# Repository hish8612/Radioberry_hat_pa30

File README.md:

# [Radioberry_hat_pa30](https://github.com/hish8612/Radioberry_hat_pa30)

beta0.2 Release

This project provides a preamplifier to drive a [30W-PA (HL2-PA30 by ji1udd)](https://github.com/ji1udd/HL2-PA30) for Radioberry-2. It will be plugged on top of the radioberry-2.<br>

#### Feature
・Preamplifire(OPA2674) based on [radioberry.hat](https://github.com/pa3gsb/Radioberry-2.x/tree/master/hardware/hat)<br>
・On board ADC(MAX11613) for measuring pa-current, temperature and pa-fwd/rev from HL2-PA30 board. <br>
・Paddle or straight key inputs and PTT(Key) inputs.<br>
・No-latency sidetone output at [local CW operation.](https://github.com/hish8612/Hermes-Lite2/tree/master/gateware/variants/radioberry_cl025_cwsidetone)<br>

#### Board View

<br>

#### Connection diagram (beta0.1)

<br>

#### HL2-PA30 modifications.

#### PA30 mesurements.

// end item

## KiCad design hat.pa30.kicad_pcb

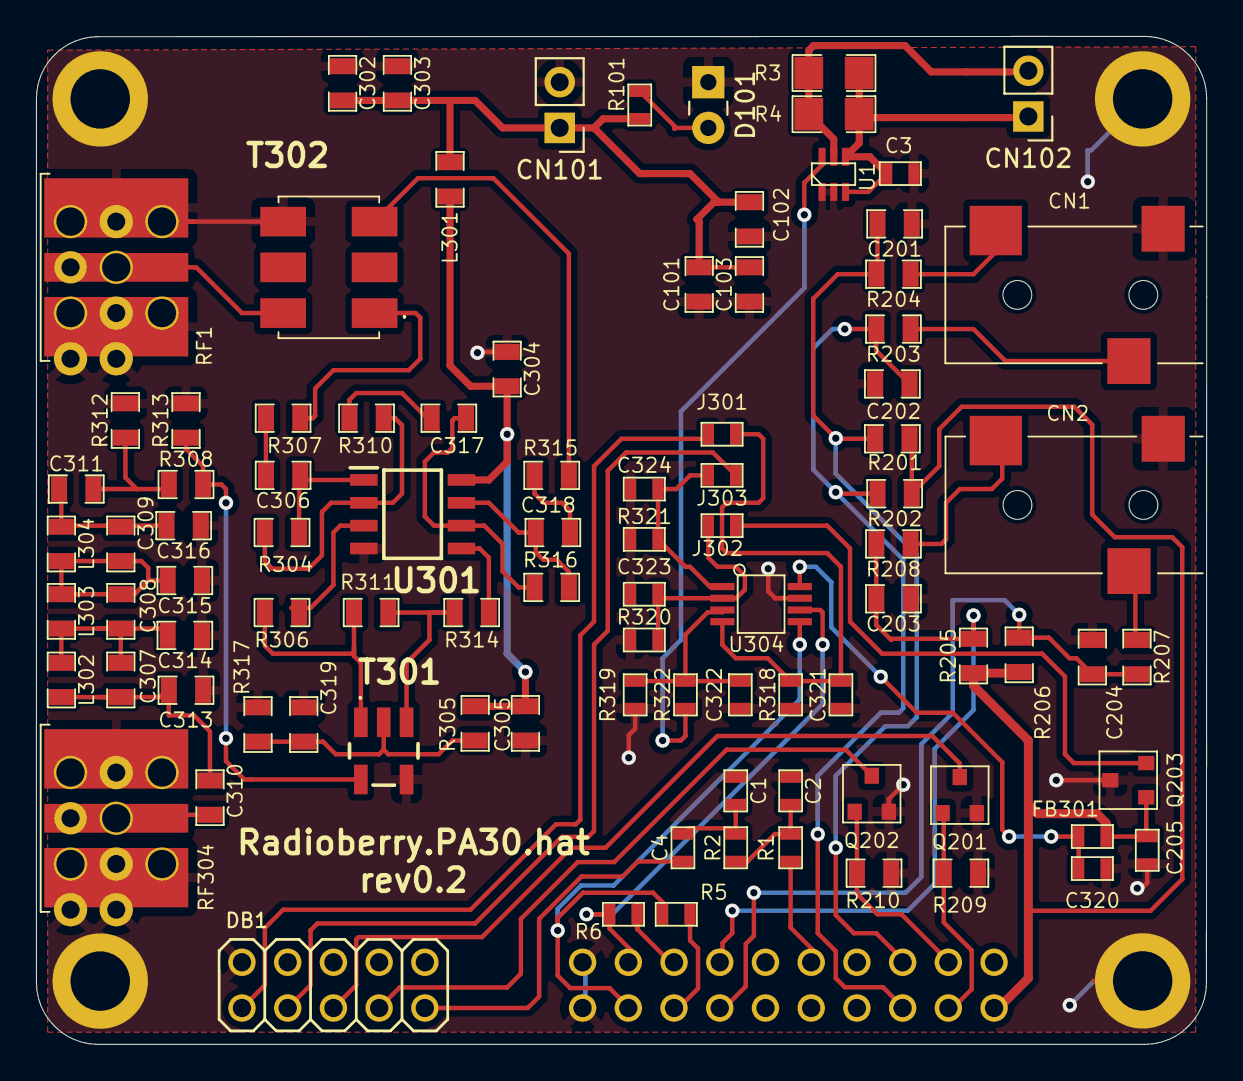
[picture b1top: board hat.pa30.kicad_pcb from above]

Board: 2 copper layers, 65.0 x 56.0 mm, 98 parts (1 on the bottom side), 58 nets.

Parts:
C1, C2, C4: 104; SMD-0603
C3, C205, C320: 0.1uF; SMD-0603
C101: 10pF; SMD-0805
C102, C315: 100pF; SMD-0805
C103: 10uF; SMD-0805
C201, C202, C203, C204: 1uF; SMD-0805
C302, C303, C304, C305, C306, C310, C311, C317, C318, C319: 0.1uF; SMD-0805
C307: 5.6pF; SMD-0805
C308: 30pF; SMD-0805
C309: 20pF; SMD-0805
C313: 82pF; SMD-0805
C314: 110pF; SMD-0805
C316: 68pF; SMD-0805
C321, C322, C323, C324: 4.7nF; SMD-0603
CN1, CN2: SJ-3523-SMT-TR; CWJACK2
CN101, CN102: PS; PinHeader_1x02_P2.54mm_Vertical
D101: LED; LED_Rectangular_W3.0mm_H2.0mm
DB1: IO10; PINHEAD_2X5
FB301: FB; SMD-0603
J301, J302, J303: JNC; SMD-0603
JP201: FEMALE_PINHEAD_PINHD-2X10; PINHEAD_2X10
L301: L_Small; SMD-0805
L302: 160nH; SMD-0805
L303, L304: 130nH; SMD-0805
MH1, MH2, MH3, MH4: DNI; m3
Q201, Q202: NUD3124; SOT23_3
Q203: MCP9700; SOT23_3
R1, R2: 560; SMD-0603
R3, R4: 0.04; SMD-1206
R5, R6: 0; SMD-0603
R101: 1.8k; SMD-0603
R201, R202, R205, R206: 2.2K; SMD-0805
R203, R204, R207, R208: 100; SMD-0805
R209, R210: 4.7K; SMD-0805
R304, R316: 510; SMD-0805
R305, R317: 1K; SMD-0805
R306, R314: 12; SMD-0805
R307, R315: 4R99; SMD-0805
R308, R312, R313: 0; SMD-0805
R310: 300; SMD-0805
R311: 200; SMD-0805
R318, R319, R320, R321: 1K; SMD-0603
R322: 270; SMD-0603
RF1, RF304: SMA; SMAEDGE_THFULL_L
T301: TC4-1T; TC41T
T302: ADT1.5-1+; ADT151
U1: INA199A1DC; PE4259
U301: OPA2674; SOIC127P600X175-8N
U304: MAX11613

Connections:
+3V3: C205.1, FB301.1, JP201.1, Q203.1, R201.2, R202.2, R205.2, R206.2
+12V: C101.1, C102.1, C103.1, C302.1, C303.1, CN101.1, L301.1, R101.1
+12VA: C304.1, C305.1, L301.2, R305.2, U301.8 (V+)
/Control/Sidetone: C4.2, DB1.9
/Control/Vfwd: DB1.3, J303.2
/Control/Vrev: DB1.1, J301.2
/Control/Vtemp: J302.2, Q203.2
EXTTR: DB1.7, Q202.3 (D)
GND: C1.2, C2.2, C3.2, C101.2, C102.2, C103.2, C201.2, C202.2, C203.2, C204.2, C205.2, C302.2, C303.2, C304.2, C305.2, C313.2, C314.2, C315.2, C316.2, C319.2, C320.2, C321.2, C322.2, C323.2, C324.2, CN1.1 (S), CN2.1 (S), CN101.2, D101.1 (K), DB1.2, DB1.4, DB1.6, DB1.8, DB1.10, JP201.19, JP201.20, MH1.1, MH2.1, MH3.1, MH4.1, Q201.2 (S), Q202.2 (S), Q203.3, R209.1, R210.1, R312.1, R313.1, R317.1, R318.1, R319.1, R320.1, R321.1, RF1.2 (Ext), RF304.2 (Ext), T301.4 (S2), T302.4 (SECONDARY_DOT), U1.1 (REF), U1.2 (GND), U301.4 (V-), U304.7 (GND)
INTTR: DB1.5, Q201.3 (D)
unnamed: C1.1, C4.1, R2.1
unnamed: C2.1, R1.1, R2.2
unnamed: C306.1, R307.1
unnamed: C306.2, R304.1, U301.1
unnamed: C307.1, C310.1, C313.1, L302.1
unnamed: C307.2, C308.1, C314.1, L302.2, L303.1
unnamed: C308.2, C309.1, C315.1, L303.2, L304.1
unnamed: C309.2, C311.2, C316.1, L304.2
unnamed: C311.1, R308.2, R312.2
unnamed: C317.1, R310.2
unnamed: C318.1, R315.2
unnamed: C318.2, R316.1, U301.7
unnamed: CN1.3 (R), R203.2
unnamed: CN1.2 (T), R204.2
unnamed: CN2.3 (R), R207.2
unnamed: CN2.2 (T), R208.2
unnamed: C3.1, CN102.1, R3.1, R4.1, U1.3 (V+), U1.4 (IN+)
unnamed: CN102.2, R3.2, R4.2, U1.5 (IN-)
unnamed: D101.2 (A), R101.2
unnamed: JP201.10, R1.2
unnamed: JP201.15, R5.1
unnamed: JP201.16, R6.2
unnamed: RF1.1 (In), T302.6 (SECONDARY)
unnamed: C310.2, RF304.1 (In)
unnamed: C319.1, R305.1, R317.2, T301.2 (PM)
unnamed: R306.2, R311.1, T301.1 (PR1)
unnamed: R311.2, R314.1, T301.3 (PR2)
unnamed: R308.1, R313.2, T301.6 (S1)
unnamed: R315.1, T302.3 (PRIMARY)
unnamed: R307.2, T302.1 (PRIMARY_DOT)
unnamed: R306.1, U301.3 (+)
unnamed: R304.2, R310.1, U301.2 (-)
unnamed: R314.2, U301.5 (+)
unnamed: C317.2, R316.2, U301.6 (-)
unnamed: C324.1, J303.1, R321.2, U304.1 (AIN0)
unnamed: C323.1, J302.1, R320.2, U304.2 (AIN1)
unnamed: C322.1, R319.2, R322.1, U304.3 (AIN2)
unnamed: C321.1, J301.1, R318.2, U304.4 (AIN3)
unnamed: C320.1, FB301.2, U304.8 (Vdd)
SCL: JP201.17, R5.2, U304.5 (SCL)
SDA: JP201.18, R6.1, U304.6 (SDA)
Vipa: R322.2, U1.6 (OUT)
dash: C202.1, JP201.5, R202.1, R203.1
dot: C201.1, JP201.6, R201.1, R204.1
key: C204.1, JP201.13, R206.1, R207.1
ptt: C203.1, JP201.14, R205.1, R208.1
rb_exttr: JP201.4, Q202.1 (G), R210.2
rb_inttr: JP201.3, Q201.1 (G), R209.2

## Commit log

2024-10-23 1st release (beta0.2)
2025-02-17 Added PA30 filter characteristics
